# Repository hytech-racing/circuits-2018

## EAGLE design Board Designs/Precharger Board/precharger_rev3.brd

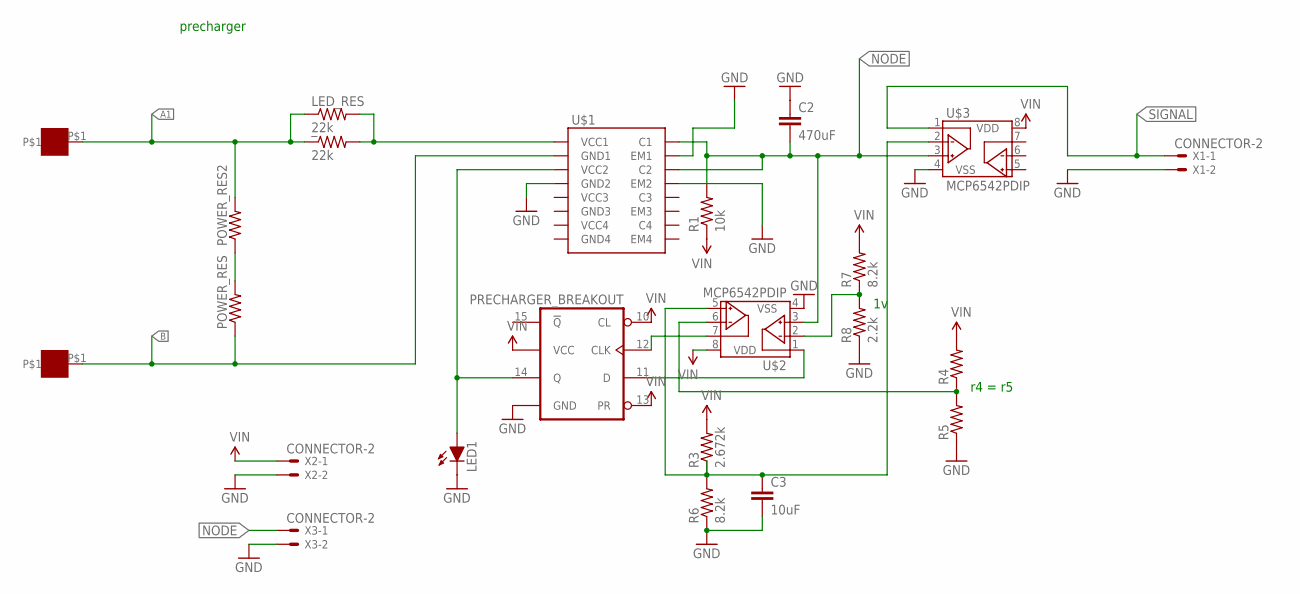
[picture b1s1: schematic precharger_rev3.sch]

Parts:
+: SOLDER_PAD; SOLDER_PAD_XSMALL
-: SOLDER_PAD; SOLDER_PAD_XSMALL
C2: 470uF; CAP-PTH-5MM
C3: 10uF; CAP-PTH-SMALL
LED1: LED-3MM
LED_RES: 22k; AXIAL-0.3
POWER_RES, POWER_RES2: RESISTOR10W; 10W_RESISTOR_VISHAY
R1: 10k; AXIAL-0.3
R3: 2.672k; AXIAL-0.3
R4, R5: RESISTORAXIAL-0.3; AXIAL-0.3
R6, R7: 8.2k; AXIAL-0.3
R8: 2.2k; AXIAL-0.3
U$1: PRECHARGER_BREAKOUT
U$2, U$3: MCP6542PDIP; DIL08
X1, X2, X3: CONNECTOR-2; MINIFIT_5566-2
_: 22k; AXIAL-0.3

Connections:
A1: +.P$1, LED_RES.P$1 (1), POWER_RES2.2, _.P$1 (1)
B: -.P$1, POWER_RES.1, U$1.2 (GND1)
GND: C2.1, C3.2, LED1.K (C), R5.P$1 (1), R6.P$1 (1), R8.P$1 (1), U$1.4 (GND2), U$1.16 (GND), U$1.29 (EM2), U$1.31 (EM1), U$2.4 (VSS), U$3.4 (VSS), X1.2, X2.2, X3.2
unnamed: LED1.A, U$1.3 (VCC2), U$1.14 (Q)
unnamed: POWER_RES.2, POWER_RES2.1
unnamed: LED_RES.P$2 (2), U$1.1 (VCC1), _.P$2 (2)
unnamed: U$1.12 (CLK), U$2.7 (VOUTB)
unnamed: U$1.11 (D), U$2.1 (VOUTA)
unnamed: C3.1, R3.P$1 (1), R6.P$2 (2), U$2.5 (VINB+), U$3.2 (VINA-)
unnamed: R4.P$1 (1), R5.P$2 (2), U$2.6 (VINB-)
unnamed: R7.P$1 (1), R8.P$2 (2), U$2.2 (VINA-)
NODE: C2.2, R1.P$2 (2), U$1.30 (C2), U$1.32 (C1), U$2.3 (VINA+), U$3.3 (VINA+), X3.1
SIGNAL: U$3.1 (VOUTA), X1.1
VIN: R1.P$1 (1), R3.P$2 (2), R4.P$2 (2), R7.P$2 (2), U$1.10 (CL), U$1.13 (PR), U$1.23 (VCC), U$2.8 (VDD), U$3.8 (VDD), X2.1

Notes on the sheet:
precharger
r4 = r5

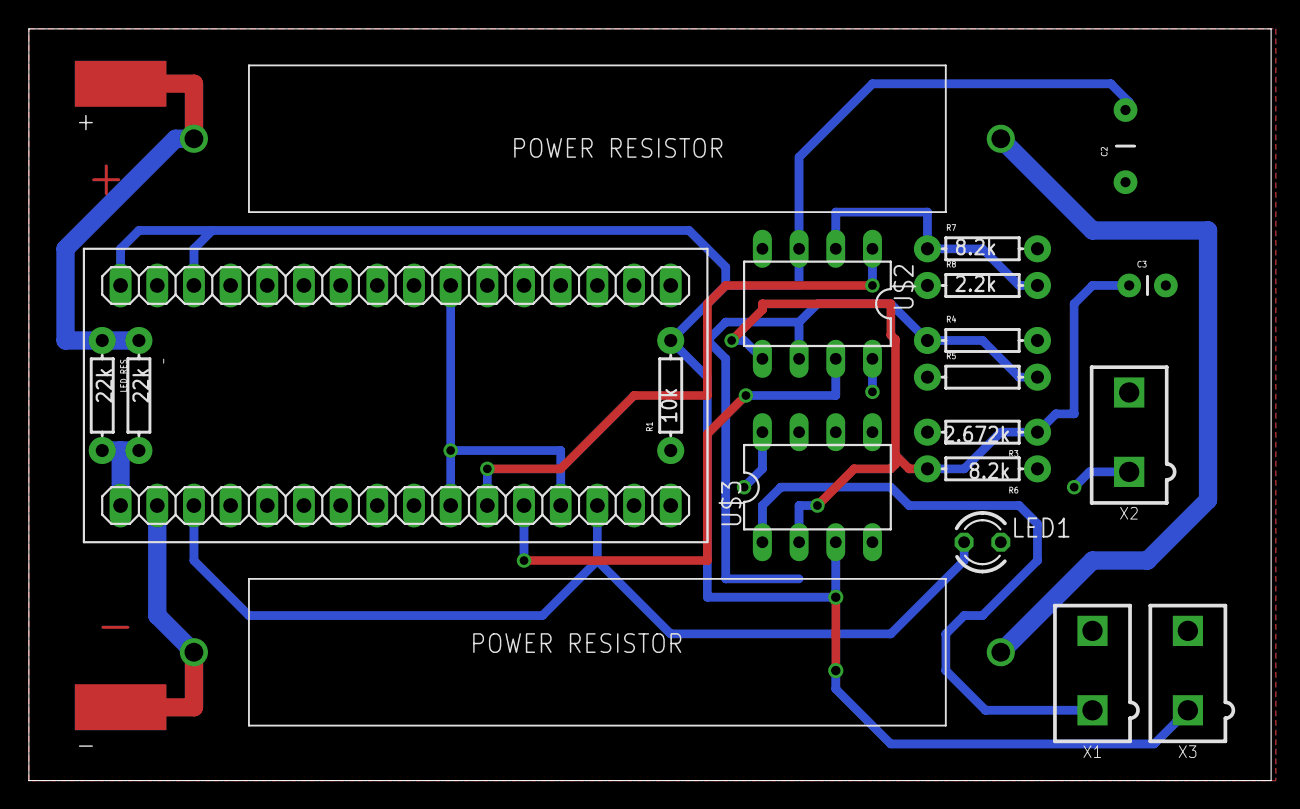
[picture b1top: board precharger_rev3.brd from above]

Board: 2 copper layers, 86.0 x 52.1 mm, 22 parts (0 on the bottom side), 14 nets.

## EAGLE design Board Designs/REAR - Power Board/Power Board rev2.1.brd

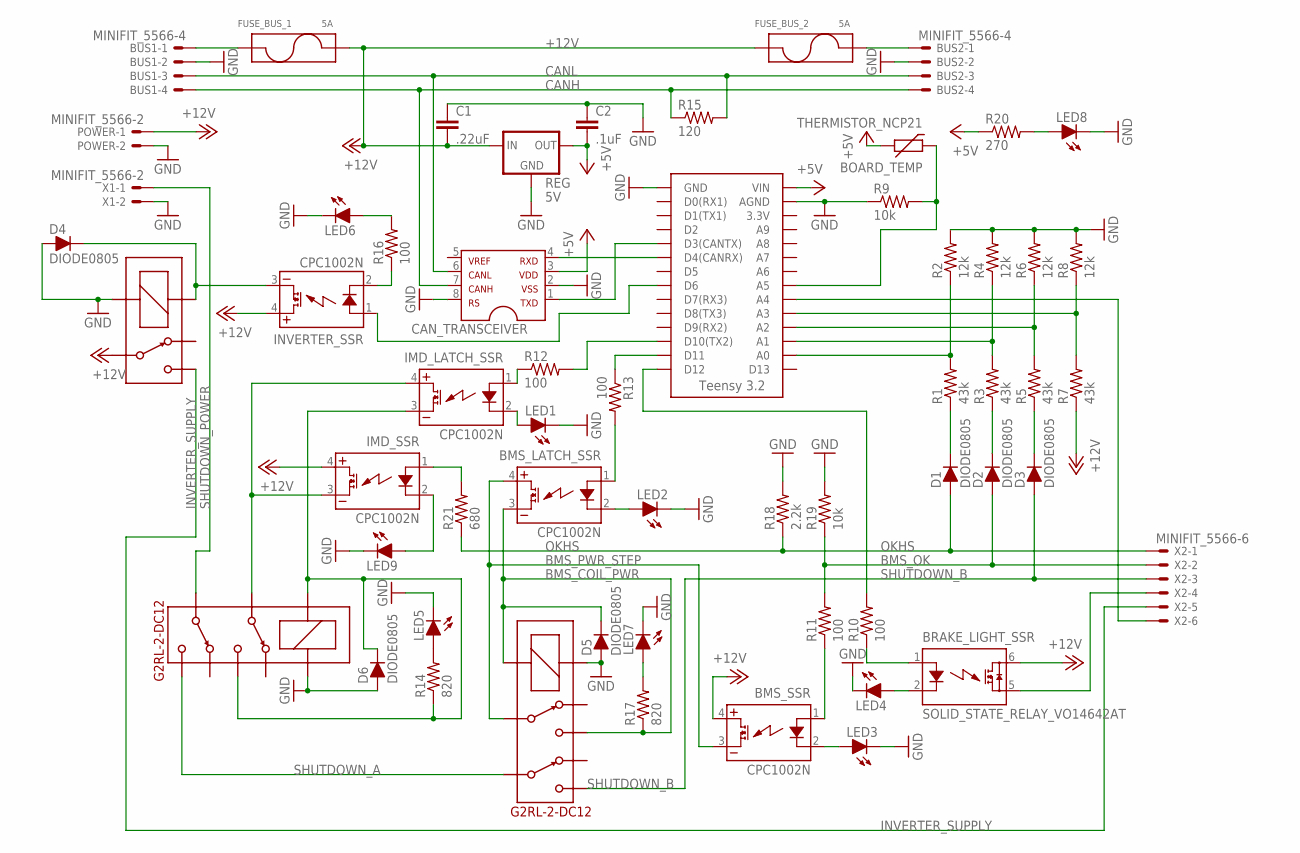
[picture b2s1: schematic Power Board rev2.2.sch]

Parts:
BMS_LATCH_SSR: CPC1002N; SOP04
BMS_SSR: CPC1002N; SOP04
BOARD_TEMP: THERMISTOR_NCP21; 0805
BRAKE_LIGHT_SSR: SOLID_STATE_RELAY_VO14642AT; DIL06
BUS1, BUS2: MINIFIT_5566-4
C1: .22uF; 0805
C2: .1uF; 0805
CAN_TRANSCEIVER: MCP2551; SOIC-08
D1, D2, D3, D4, D5, D6: DIODE0805; 0805_D
FUSE_BUS_1, FUSE_BUS_2: 5A; MINI-BLADE_FUSE_HOLDER
IMD_LATCH_SSR: CPC1002N; SOP04
IMD_SHUTDOWN, IMD_SHUTDOWN1: G2RL-2-DC12; G2RL-2
IMD_SSR: CPC1002N; SOP04
INVERTER_SSR: CPC1002N; SOP04
LED1, LED2, LED3, LED4, LED5, LED6, LED7, LED8, LED9: LED-0805; LED-805
POWER: MINIFIT_5566-2
R1, R3, R5, R7: 43k; 0805
R2, R4, R6, R8: 12k; 0805
R9, R19: 10k; 0805
R10, R11, R12, R13, R16: 100; 0805
R14, R17: 820; 0805
R15: 120; 0805
R18: 2.2k; 0805
R20: 270; 0805
R21: 680; 0805
REG: 5V; SOT223
U$1: G5LE; ZF112
U$3: TEENSY_3.2_SIMPLE
X1: MINIFIT_5566-2
X2: MINIFIT_5566-6

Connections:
12VSUPPLY_READ: R7.2, R8.1, U$3.A3
12V_F1: BUS1.1, FUSE_BUS_1.L1 (P1), FUSE_BUS_1.L2 (P1)
12V_F2: BUS2.1, FUSE_BUS_2.R1 (P2), FUSE_BUS_2.R2 (P2)
+5V: BOARD_TEMP.1, C2.2, CAN_TRANSCEIVER.3, R20.1, REG.3 (OUT), U$3.VIN
+12V: BMS_SSR.4 (DC+), BRAKE_LIGHT_SSR.6 (IO1), C1.2, FUSE_BUS_1.R1 (P2), FUSE_BUS_1.R2 (P2), FUSE_BUS_2.L1 (P1), FUSE_BUS_2.L2 (P1), IMD_SSR.4 (DC+), INVERTER_SSR.4 (DC+), POWER.1, R7.1, REG.1 (IN), U$1.P
BMS_COIL_PWR: BMS_LATCH_SSR.3 (DC-), D5.C, IMD_SHUTDOWN1.4, IMD_SHUTDOWN1.COIL-, R17.1
BMS_OK: D2.A, R11.2, R19.1, X2.2
BMS_OK_READ: R3.2, R4.1, U$3.A1
BMS_PWR_STEP: BMS_LATCH_SSR.4 (DC+), BMS_SSR.3 (DC-), IMD_SHUTDOWN1.3
CANH: BUS1.4, BUS2.4, CAN_TRANSCEIVER.7, R15.1
CANL: BUS1.3, BUS2.3, CAN_TRANSCEIVER.6, R15.2
GND: BUS1.2, BUS2.2, C1.1, C2.1, CAN_TRANSCEIVER.2, CAN_TRANSCEIVER.8, D4.A, D5.A, D6.A, IMD_SHUTDOWN.COIL+, IMD_SHUTDOWN1.COIL+, LED1.C, LED2.C, LED3.C, LED4.C, LED5.C, LED6.C, LED7.C, LED8.C, LED9.C, POWER.2, R2.2, R4.2, R6.2, R8.2, R9.1, R18.2, R19.2, REG.2 (GND), REG.4 (GND), U$1.2 (COIL-), U$3.AGND, U$3.GND, X1.2
INVERTER_SUPPLY: U$1.S, X2.5
unnamed: IMD_LATCH_SSR.2 (CONTROL-), LED1.A
unnamed: CAN_TRANSCEIVER.4, U$3.D4(CANRX)
unnamed: CAN_TRANSCEIVER.1, U$3.D3(CANTX)
unnamed: BRAKE_LIGHT_SSR.5 (IO2), X2.4
unnamed: IMD_LATCH_SSR.1 (CONTROL+), R12.1
unnamed: D6.C, IMD_LATCH_SSR.3 (DC-), IMD_SHUTDOWN.4, IMD_SHUTDOWN.COIL-, R14.1
unnamed: BRAKE_LIGHT_SSR.2 (LED-), LED4.A
unnamed: R12.2, U$3.D10(TX2)
unnamed: BMS_SSR.2 (CONTROL-), LED3.A
unnamed: BMS_LATCH_SSR.1 (CONTROL+), R13.2
unnamed: R10.2, U$3.D12
unnamed: R13.1, U$3.D11
unnamed: BOARD_TEMP.2, R9.2, U$3.A5
unnamed: BMS_LATCH_SSR.2 (CONTROL-), LED2.A
unnamed: BRAKE_LIGHT_SSR.1 (LED+), R10.1
unnamed: BMS_SSR.1 (CONTROL+), R11.1
unnamed: LED5.A, R14.2
unnamed: U$3.A4, X2.6
unnamed: INVERTER_SSR.1 (CONTROL+), U$3.D6
unnamed: D1.C, R1.1
unnamed: D2.C, R3.1
unnamed: D3.C, R5.1
unnamed: D4.C, INVERTER_SSR.3 (DC-), U$1.1 (COIL+)
unnamed: INVERTER_SSR.2 (CONTROL-), R16.1
unnamed: LED6.A, R16.2
unnamed: LED8.A, R20.2
unnamed: IMD_LATCH_SSR.4 (DC+), IMD_SHUTDOWN.3, IMD_SSR.3 (DC-)
unnamed: IMD_SSR.1 (CONTROL+), R21.2
unnamed: LED7.A, R17.2
unnamed: IMD_SSR.2 (CONTROL-), LED9.A
OKHS: D1.A, R18.1, R21.1, X2.1
OKHS_READ: R1.2, R2.1, U$3.A0
SHUTDOWN_A: IMD_SHUTDOWN.5, IMD_SHUTDOWN1.6
SHUTDOWN_B: D3.A, IMD_SHUTDOWN1.5, X2.3
SHUTDOWN_OUT_READ: R5.2, R6.1, U$3.A2
SHUTDOWN_POWER: IMD_SHUTDOWN.6, X1.1

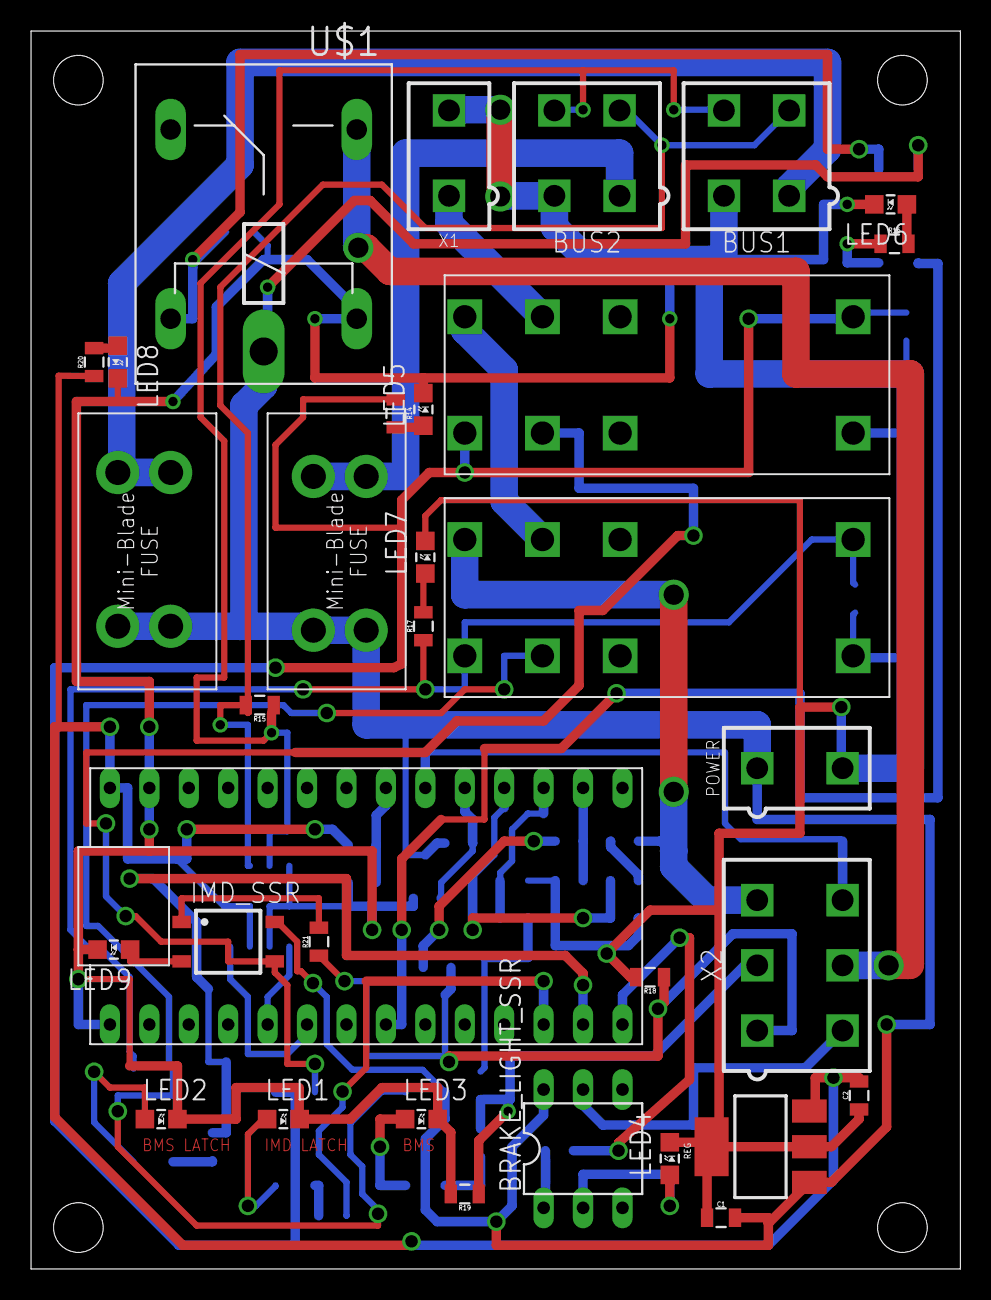
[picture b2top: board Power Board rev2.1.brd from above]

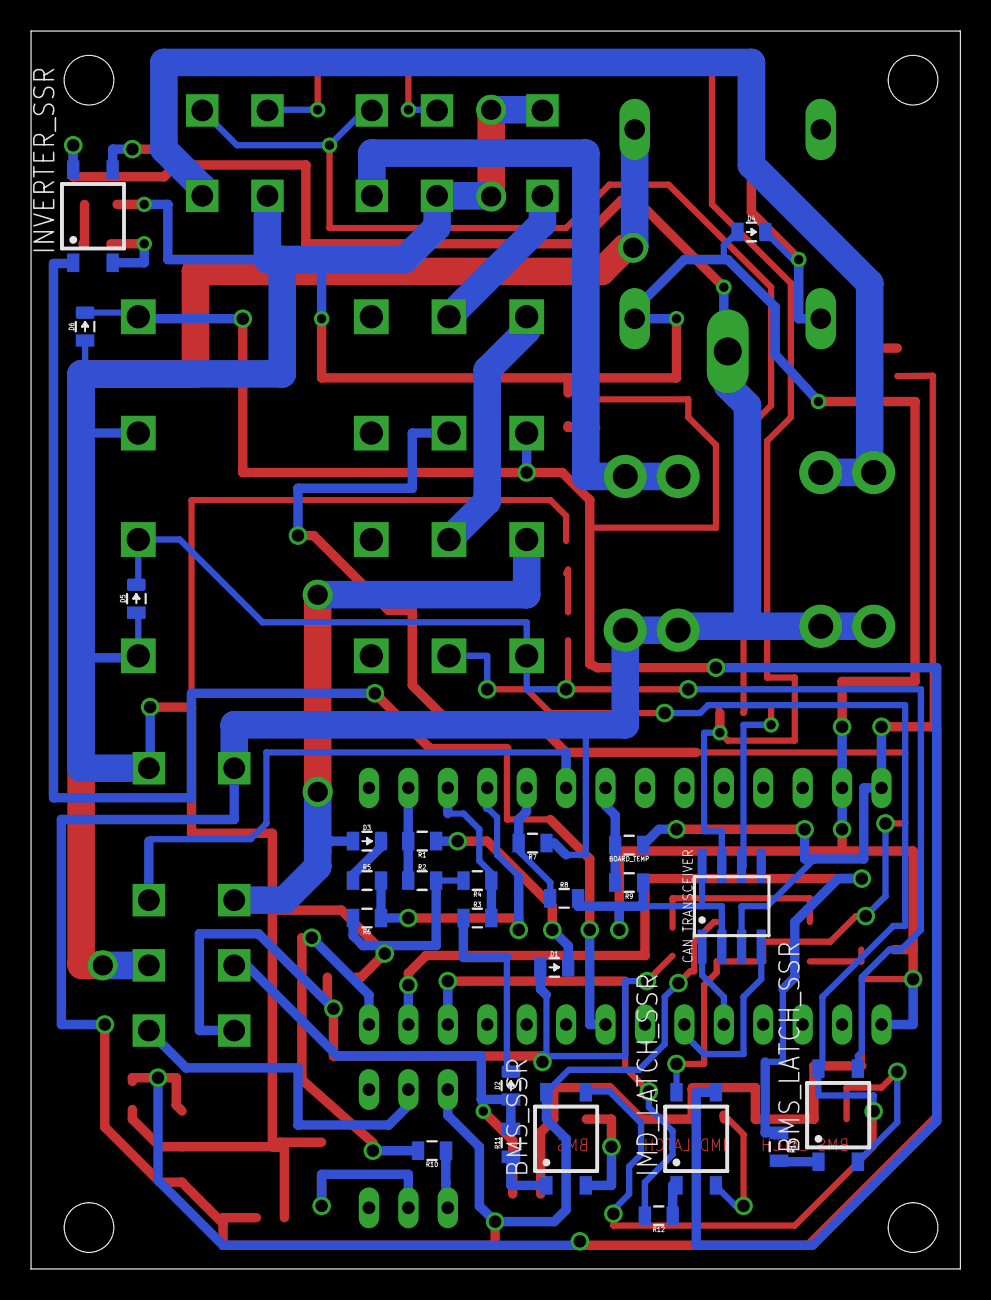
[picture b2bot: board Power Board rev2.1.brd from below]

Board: 2 copper layers, 59.9 x 79.7 mm, 58 parts (25 on the bottom side), 49 nets.

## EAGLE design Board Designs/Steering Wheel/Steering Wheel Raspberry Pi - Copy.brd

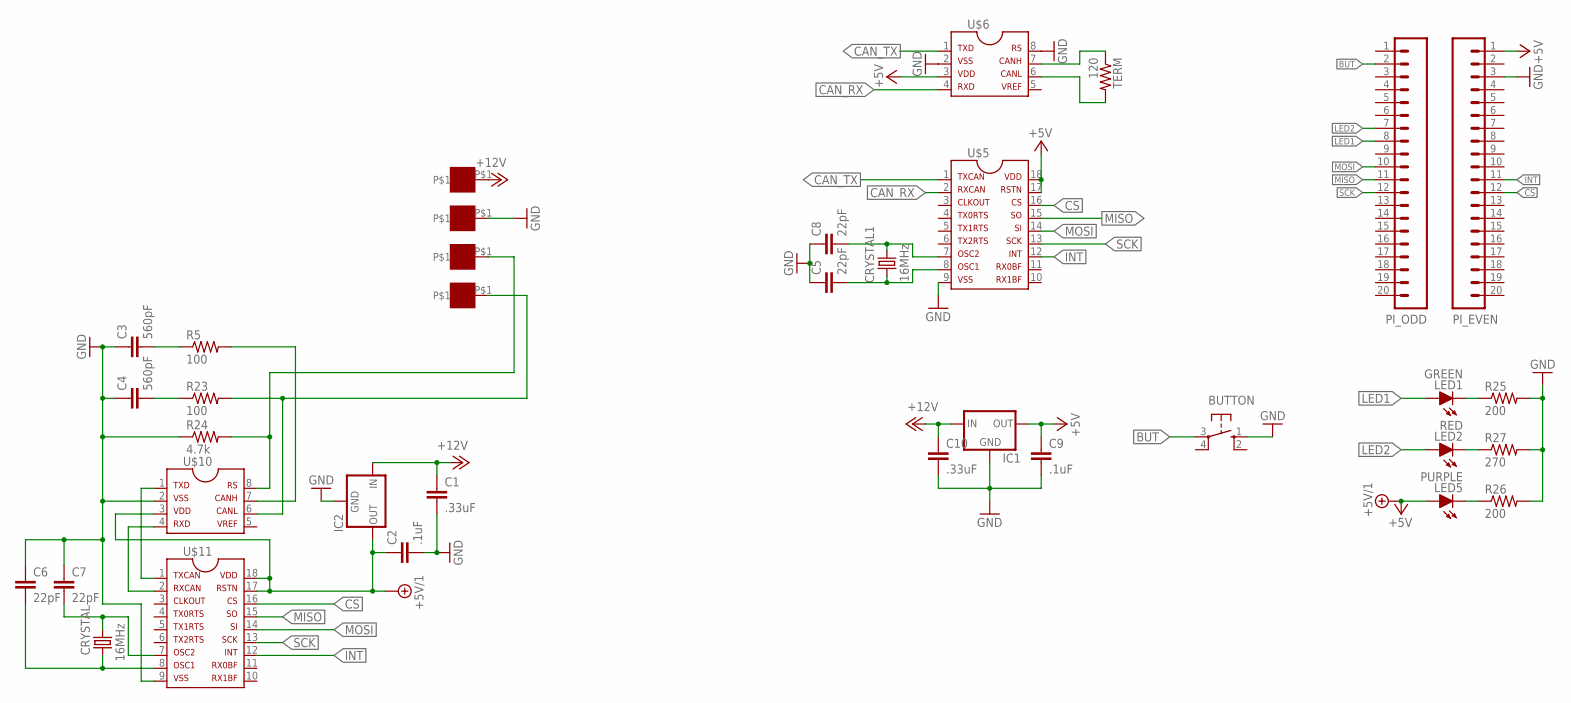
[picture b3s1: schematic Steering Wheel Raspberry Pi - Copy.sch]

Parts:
BUTTON: BTN_10-XX; B3F-10XX
C1, C10: .33uF; 0805
C2, C9: .1uF; 0805
C3, C4: 560pF; 0805
C5, C6, C7, C8: 22pF; 0805
CRYSTAL, CRYSTAL1: 16MHz; HC49UP
IC1, IC2: OKI-78SR-5/1.5-W36-C_VERT; TO-220
LED1: GREEN; LED-805
LED2: RED; LED-805
LED5: PURPLE; LED-805
PI_EVEN: M20; 1X20
PI_ODD: M20; 1X20
R5, R23: 100; 0805
R24: 4.7k; 0805
R25, R26: 200; 0805
R27: 270; 0805
TERM: 120; 0805
U$1, U$2, U$3, U$4: SOLDER_PAD; SOLDER_PAD_XSMALL
U$5, U$11: MCP2515SMD; SOIC-18W
U$6, U$10: MCP2551; SOIC-08

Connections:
+5V: C9.1, IC1.3 (OUT), LED5.A, PI_EVEN.1, U$5.17, U$5.18, U$6.3
+5V/1: C2.1, IC2.3 (OUT), U$10.3, U$11.17, U$11.18
+12V: C1.1, C10.1, IC1.1 (IN), IC2.1 (IN), U$1.P$1
BUT: BUTTON.3, PI_ODD.2
CAN-H: R5.2, U$10.7
CAN-L: R23.2, U$4.P$1, U$10.6
CAN_RX: U$5.2, U$6.4
CAN_TX: U$5.1, U$6.1
CS: PI_EVEN.12, U$5.16, U$11.16
GND: BUTTON.1 (S), C1.2, C2.2, C3.1, C4.1, C5.1, C6.1, C7.1, C8.1, C9.2, C10.2, IC1.2 (GND), IC2.2 (GND), PI_EVEN.3, R24.1, R25.2, R26.2, R27.2, U$2.P$1, U$5.9, U$6.2, U$6.8, U$10.2, U$11.9
INT: PI_EVEN.11, U$5.12, U$11.12
LED1: LED1.A, PI_ODD.8
LED2: LED2.A, PI_ODD.7
MISO: PI_ODD.11, U$5.15, U$11.15
MOSI: PI_ODD.10, U$5.14, U$11.14
unnamed: C8.2, CRYSTAL1.1, U$5.7
unnamed: C5.2, CRYSTAL1.2, U$5.8
unnamed: TERM.1, U$6.7
unnamed: TERM.2, U$6.6
unnamed: U$10.1, U$11.1
unnamed: U$10.4, U$11.2
unnamed: C6.2, CRYSTAL.2, U$11.8
unnamed: R24.2, U$3.P$1, U$10.8
unnamed: C7.2, CRYSTAL.1, U$11.7
unnamed: C3.2, R5.1
unnamed: C4.2, R23.1
unnamed: LED1.C, R25.1
unnamed: LED5.C, R26.1
unnamed: LED2.C, R27.1
SCK: PI_ODD.12, U$5.13, U$11.13

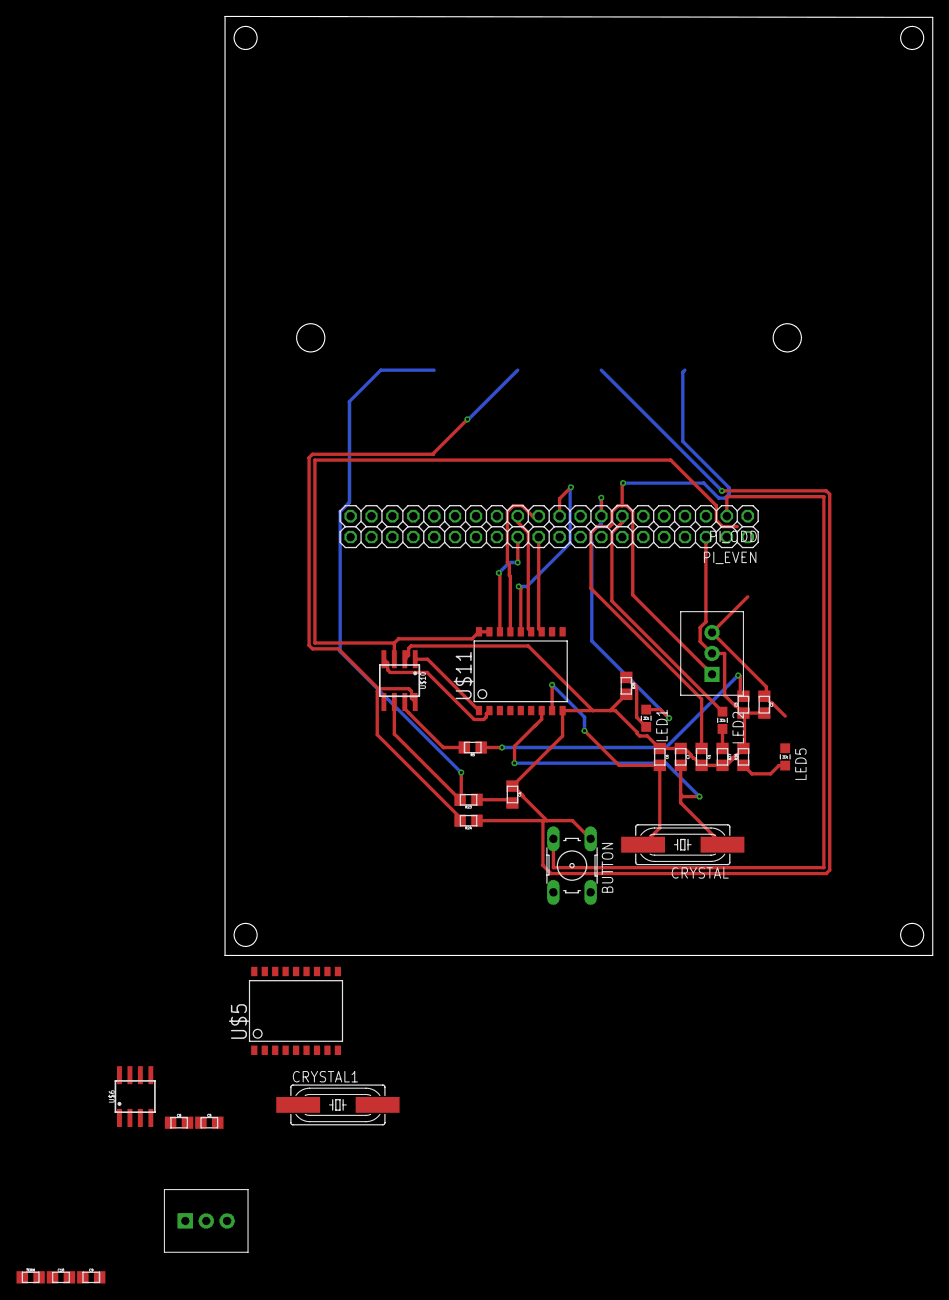
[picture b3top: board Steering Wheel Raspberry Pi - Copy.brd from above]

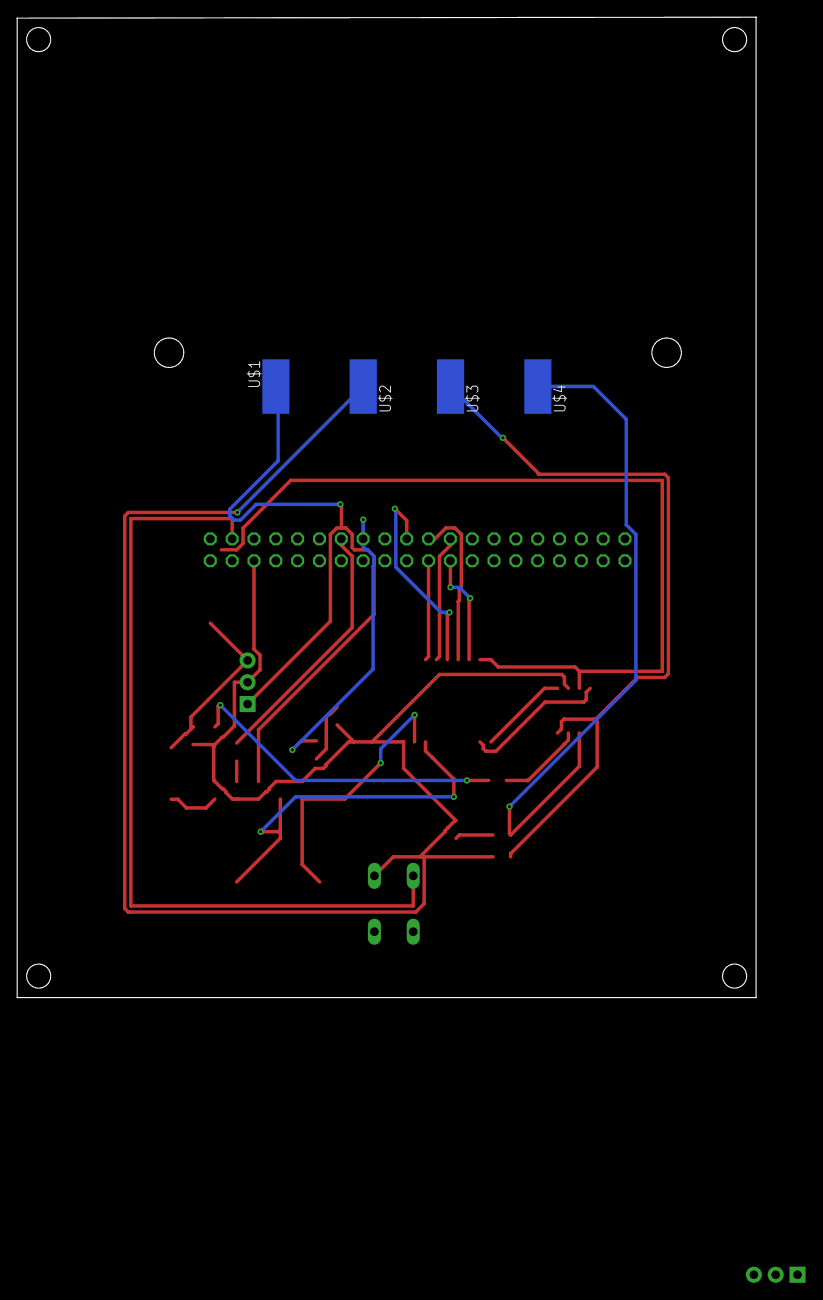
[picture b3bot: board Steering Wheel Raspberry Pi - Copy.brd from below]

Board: 2 copper layers, 86.0 x 114.1 mm, 35 parts (4 on the bottom side), 30 nets.

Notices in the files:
parts and their libraries:
SparkFun-FreqCtrl: Licensing: Creative Commons ShareAlike 4.0 International - https://creativecommons.org/licenses/by-sa/4.0
